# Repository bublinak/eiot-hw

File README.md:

# eiot-hw
Schemes, drawings &amp; other documentation

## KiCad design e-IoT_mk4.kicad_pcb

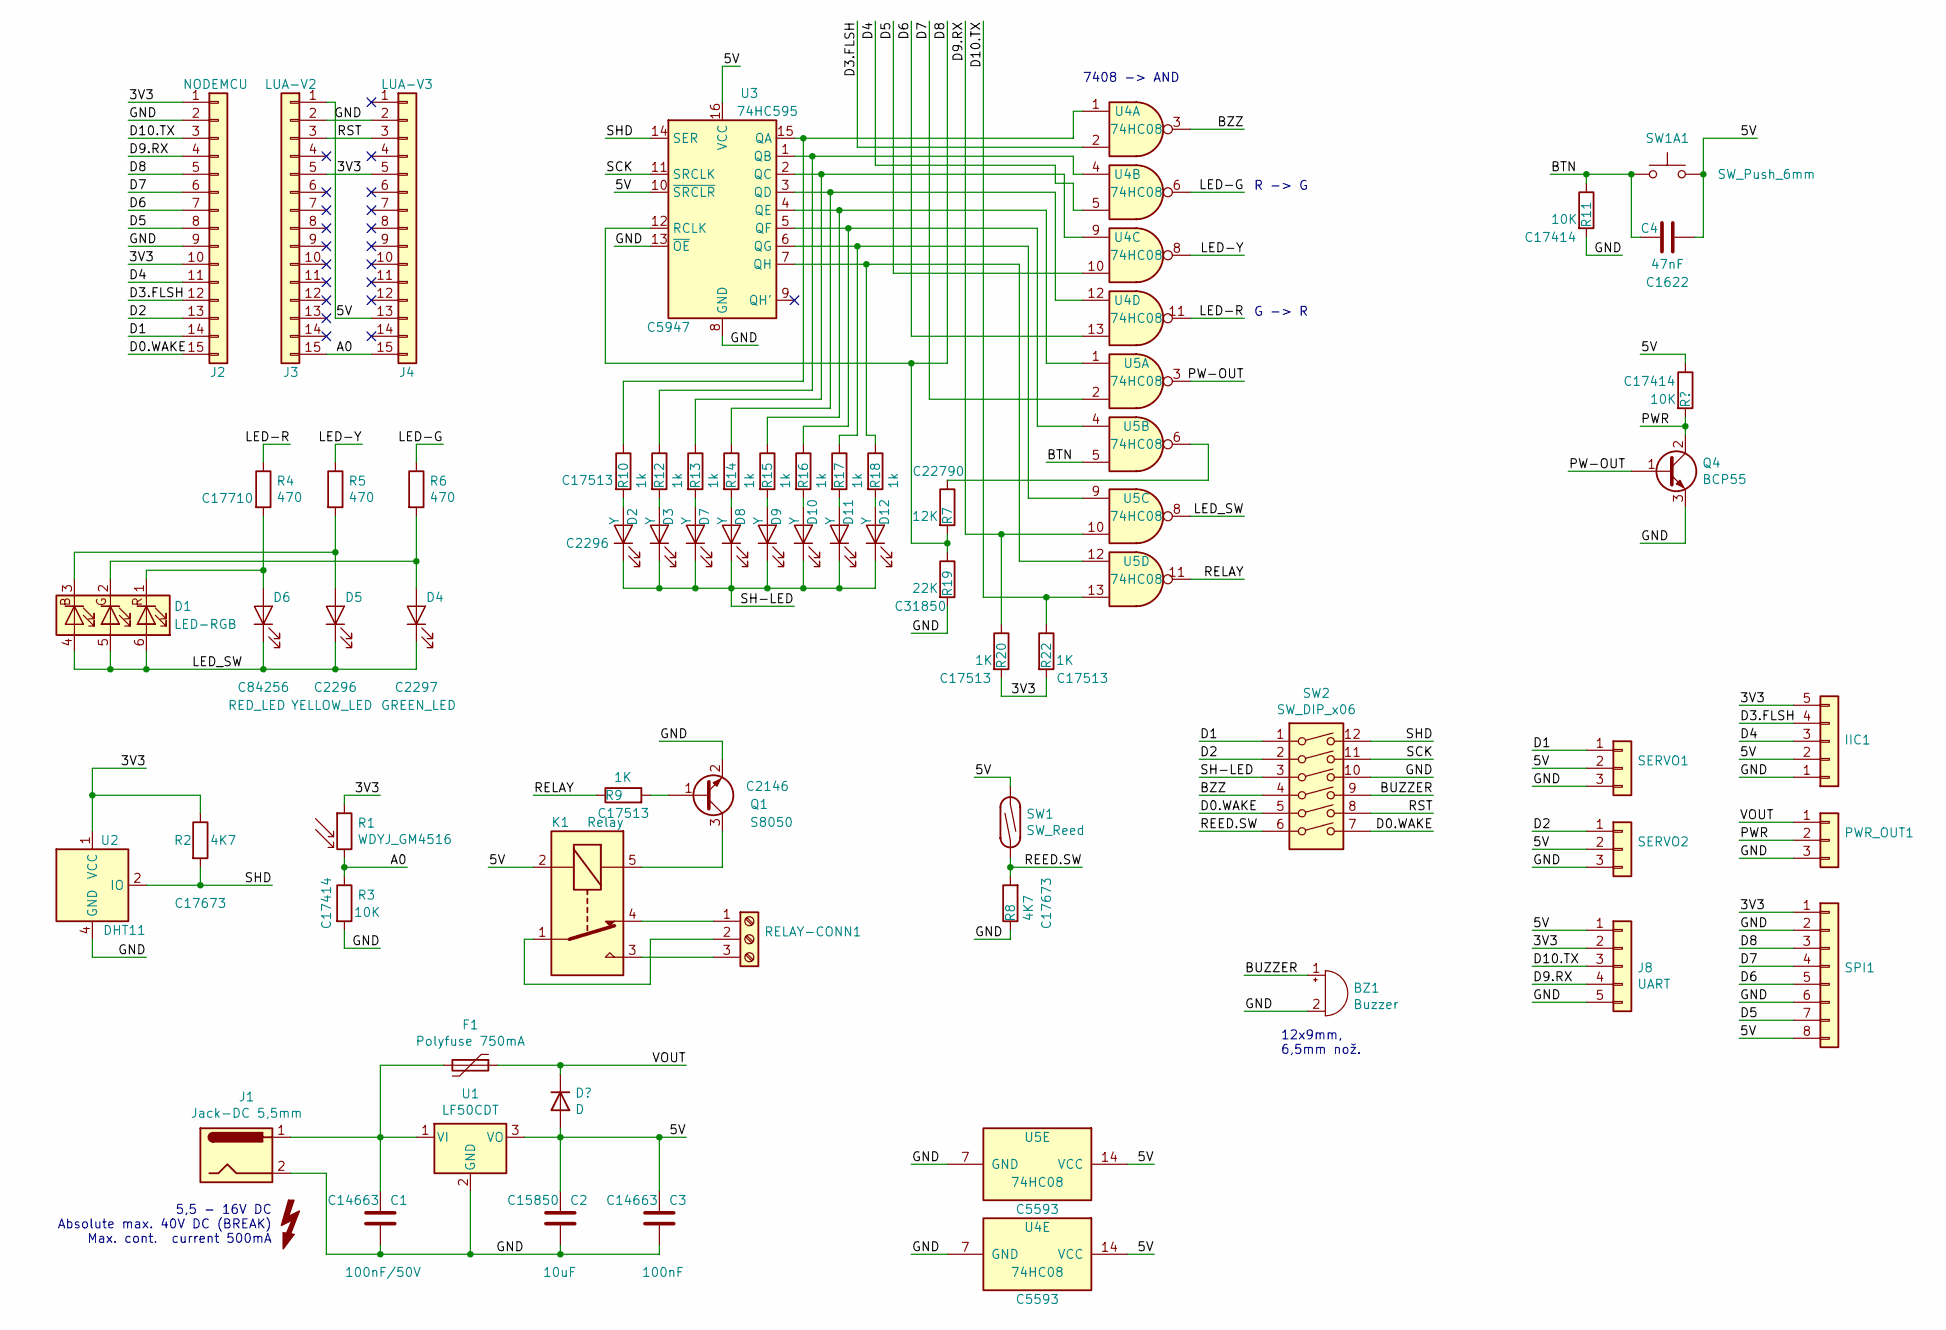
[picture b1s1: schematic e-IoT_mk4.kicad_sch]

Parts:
BZ1: Buzzer; MagneticBuzzer_ProSignal_ABT-410-RC
C1: 100nF/50V; C_0603_1608Metric; LCSC C14663
C2: 10uF; C_0805_2012Metric_Pad1.15x1.40mm_HandSolder; LCSC C15850
C3: 100nF; C_0603_1608Metric_Pad1.05x0.95mm_HandSolder; LCSC C14663
C4: 47nF; C_0603_1608Metric_Pad1.05x0.95mm_HandSolder; LCSC C1622
D1: LED-RGB; LED_RGB_5050-6
D2, D3, D7, D8, D9, D10, D11, D12: Y; LED_0805_2012Metric_Castellated; LCSC C2296
D4: GREEN_LED; LED_0805_2012Metric_Castellated; LCSC C2297
D5: YELLOW_LED; LED_0805_2012Metric_Castellated; LCSC C2296
D6: RED_LED; LED_0805_2012Metric_Castellated; LCSC C84256
F1: Polyfuse 750mA; Fuse_1812_4532Metric_Pad1.30x3.40mm_HandSolder
IIC1: PinSocket_1x05_P2.54mm_Horizontal
J1: Jack-DC 5,5mm; BarrelJack_Horizontal
J2: NODEMCU; PinSocket_1x15_P2.54mm_Vertical
J3: LUA-V2; PinSocket_1x15_P2.54mm_Vertical
J4: LUA-V3; PinSocket_1x15_P2.54mm_Vertical
J8: UART; PinHeader_1x05_P2.54mm_Vertical
K1: Relay; Relay_SPDT_SANYOU_SRD_Series_Form_C
PWR_OUT1: JST_XH_S3B-XH-A-1_1x03_P2.50mm_Horizontal
Q1: S8050; SOT-23; LCSC C2146
Q4: BCP55; SOT-223
R1: WDYJ_GM4516; R_LDR_4.9x4.2mm_P2.54mm_Vertical
R2, R8: 4K7; R_0805_2012Metric_Pad1.15x1.40mm_HandSolder; LCSC C17673
R3, R11: 10K; R_0805_2012Metric_Pad1.15x1.40mm_HandSolder; LCSC C17414
R4, R5, R6: 470; R_0805_2012Metric_Pad1.15x1.40mm_HandSolder; LCSC C17710
R7: 12K; R_0603_1608Metric; LCSC C22790
R9, R20, R22: 1K; R_0805_2012Metric_Pad1.15x1.40mm_HandSolder; LCSC C17513
R10, R12, R13, R14, R15, R16, R17, R18: 1k; R_0805_2012Metric_Pad1.15x1.40mm_HandSolder; LCSC C17513
R19: 22K; R_0603_1608Metric; LCSC C31850
RELAY-CONN1: Screw_Terminal_01x03; TerminalBlock_bornier-3_P5.08mm
SERVO1, SERVO2: PinHeader_1x03_P2.54mm_Vertical
SPI1: PinSocket_1x08_P2.54mm_Horizontal
SW1: SW_Reed; Crystal_AT310_D3.0mm_L10.0mm_Horizontal
SW1A1: SW_Push_6mm; SW_PUSH_6mm_H5mm
SW2: SW_DIP_x06; DIP-12_W7.62mm_Socket_LongPads
U1: LF50CDT; TO-252-2
U2: DHT11; Aosong_DHT11_5.5x12.0_P2.54mm
U3: 74HC595; SOIC-16_3.9x9.9mm_P1.27mm; LCSC C5947
U4: 74HC08; SOIC-14_3.9x8.7mm_P1.27mm
U5: 74HC08

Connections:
/3V3: IIC1.5, J2.1, J2.10, J3.5, J4.5, J8.2, R1.1, R2.1, R20.2, R22.2, SPI1.1, U2.1 (VCC)
/5V: C2.1, C3.1, C4.1, IIC1.2, J3.1, J4.13, J8.1, K1.2, SERVO1.2, SERVO2.2, SPI1.8, SW1.1, SW1A1.2, U1.3 (VO), U3.10 (~SRCLR), U3.16 (VCC), U4.14 (VCC), U5.14 (VCC)
/A0: J3.15, J4.15, R1.2, R3.1
/BTN: C4.2, R11.1, SW1A1.1, U5.5
/BUZZER: BZ1.1 (-), SW2.9
/BZZ: SW2.4, U4.3
/D0.WAKE: J2.15, SW2.5, SW2.7
/D1: J2.14, SERVO1.1, SW2.1
/D2: J2.13, SERVO2.1, SW2.2
/D3.FLSH: IIC1.4, J2.12, U4.2
/D4: IIC1.3, J2.11, U4.5
/D5: J2.8, SPI1.7, U4.10
/D6: J2.7, SPI1.5, U4.13
/D7: J2.6, SPI1.4, U5.2
/D8: J2.5, R7.2, R19.1, SPI1.3, U3.12 (RCLK)
/D9.RX: J2.4, J8.4, R20.1, U5.10
/D10.TX: J2.3, J8.3, R22.1, U5.13
/GND: BZ1.2 (+), C1.2, C2.2, C3.2, IIC1.1, J1.2, J2.2, J2.9, J3.2, J4.2, J8.5, PWR_OUT1.3, Q1.2 (E), Q4.3 (E), R3.2, R8.1, R11.2, R19.2, SERVO1.3, SERVO2.3, SPI1.2, SPI1.6, SW2.10, U1.2 (GND), U2.4 (GND), U3.8 (GND), U3.13 (~OE), U4.7 (GND), U5.7 (GND)
/LED-G: R6.1, U4.6
/LED-R: R4.1, U4.11
/LED-Y: R5.1, U4.8
/LED_SW: D1.4 (BA), D1.5 (GA), D1.6 (RA), D4.1 (K), D5.1 (K), D6.1 (K), U5.8
/PW-OUT: Q4.1 (B), U5.3
/PWR: PWR_OUT1.2, Q4.2 (C), Q4.4 (C)
/REED.SW: R8.2, SW1.2, SW2.6
/RELAY: R9.1, U5.11
/RST: J3.3, J4.3, SW2.8
/SCK: SW2.11, U3.11 (SRCLK)
/SH-LED: D2.1 (K), D3.1 (K), D7.1 (K), D8.1 (K), D9.1 (K), D10.1 (K), D11.1 (K), D12.1 (K), SW2.3
/SHD: R2.2, SW2.12, U2.2 (IO), U3.14 (SER)
/VI: F1.1, PWR_OUT1.1
unnamed: C1.1, F1.2, J1.1, U1.1 (VI)
unnamed: D1.1 (RK), D6.2 (A), R4.2
unnamed: D1.2 (GK), D4.2 (A), R6.2
unnamed: D1.3 (BK), D5.2 (A), R5.2
unnamed: D2.2 (A), R10.2
unnamed: D3.2 (A), R12.2
unnamed: D7.2 (A), R13.2
unnamed: D8.2 (A), R14.2
unnamed: D9.2 (A), R15.2
unnamed: D10.2 (A), R16.2
unnamed: D11.2 (A), R17.2
unnamed: D12.2 (A), R18.2
unnamed: K1.1, RELAY-CONN1.2
unnamed: K1.3, RELAY-CONN1.3
unnamed: K1.4, RELAY-CONN1.1
unnamed: K1.5, Q1.3 (C)
unnamed: Q1.1 (B), R9.2
unnamed: R7.1, U5.6
unnamed: R10.1, U3.15 (QA), U4.1
unnamed: R12.1, U3.1 (QB), U4.4
unnamed: R13.1, U3.2 (QC), U4.9
unnamed: R14.1, U3.3 (QD), U4.12
unnamed: R15.1, U3.4 (QE), U5.1
unnamed: R16.1, U3.5 (QF), U5.4
unnamed: R17.1, U3.6 (QG), U5.9
unnamed: R18.1, U3.7 (QH), U5.12

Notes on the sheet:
5,5 - 16V DC Absolute max. 40V DC (BREAK) Max. cont. current 500mA
R -> G
12x9mm, 6,5mm nož.
7408 -> AND
G -> R

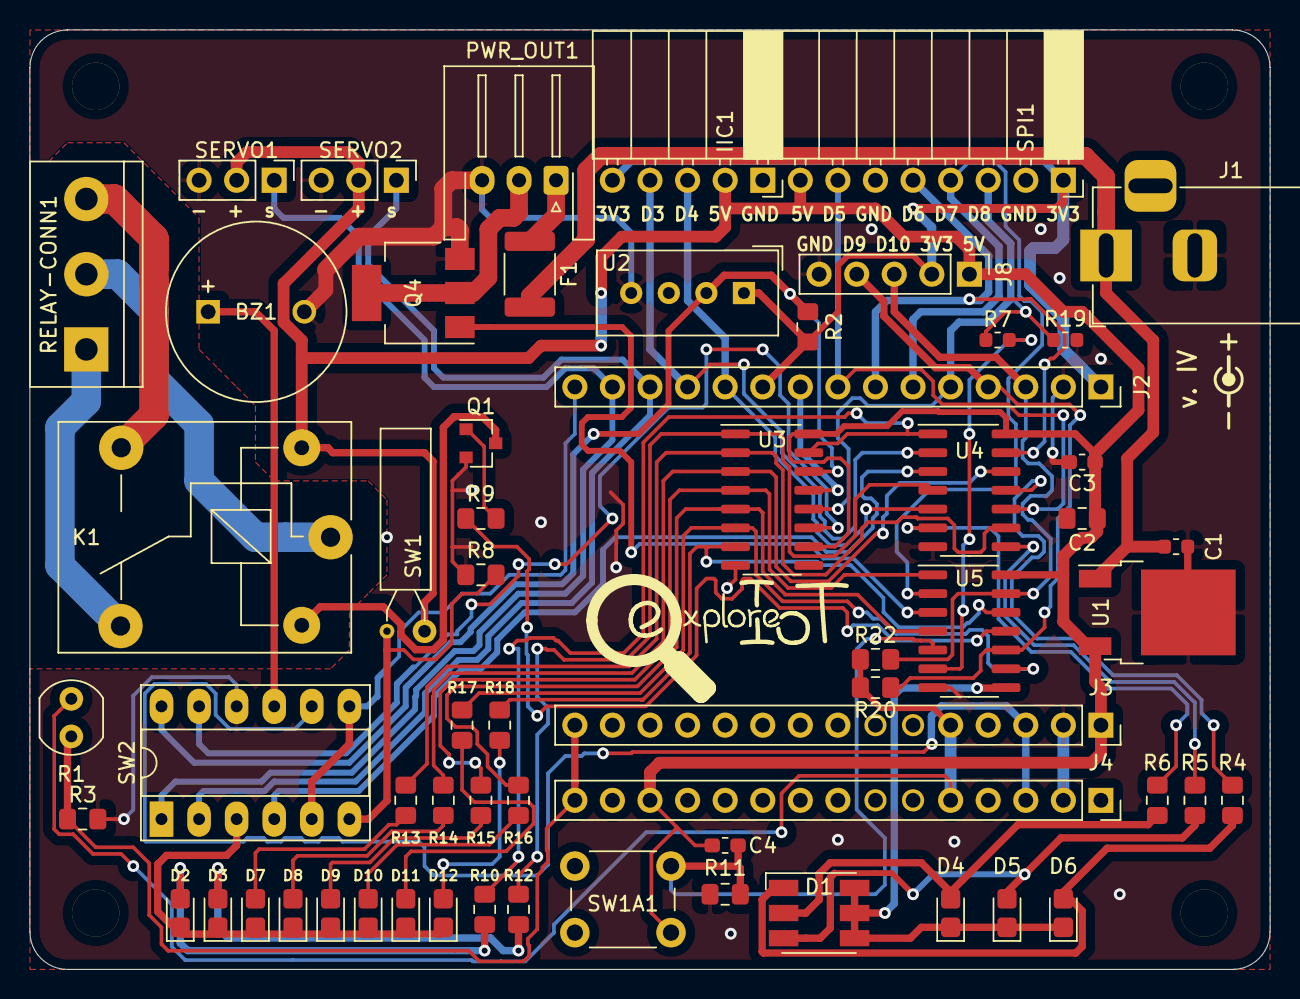
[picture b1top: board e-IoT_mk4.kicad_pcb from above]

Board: 2 copper layers, 83.8 x 63.5 mm, 61 parts (0 on the bottom side), 57 nets.

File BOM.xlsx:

Comment | Designator | Footprint | LCSC
10K | R3 | Resistor_SMD:R_0805_2012Metric_Pad1.15x1.40mm_HandSolder | C17414
RED_LED | D6 | LED_SMD:LED_0805_2012Metric_Castellated | C84256
YELLOW_LED | D5 | LED_SMD:LED_0805_2012Metric_Castellated | C2296
GREEN_LED | D4 | LED_SMD:LED_0805_2012Metric_Castellated | C2297
470 | R4 | Resistor_SMD:R_0805_2012Metric_Pad1.15x1.40mm_HandSolder | C17710
4K7 | R2 | Resistor_SMD:R_0805_2012Metric_Pad1.15x1.40mm_HandSolder | C17673
74HC595 | U3 | Package_SO:SOIC-16_3.9x9.9mm_P1.27mm | C5947
1K | R9 | Resistor_SMD:R_0805_2012Metric_Pad1.15x1.40mm_HandSolder | C17513
S8050 | Q1 | Package_TO_SOT_SMD:SOT-23 | C2146
470 | R5 | Resistor_SMD:R_0805_2012Metric_Pad1.15x1.40mm_HandSolder | C17710
470 | R6 | Resistor_SMD:R_0805_2012Metric_Pad1.15x1.40mm_HandSolder | C17710
1k | R10 | Resistor_SMD:R_0805_2012Metric_Pad1.15x1.40mm_HandSolder | C17513
Y | D2 | LED_SMD:LED_0805_2012Metric_Castellated | C2296
1k | R12 | Resistor_SMD:R_0805_2012Metric_Pad1.15x1.40mm_HandSolder | C17513
1k | R13 | Resistor_SMD:R_0805_2012Metric_Pad1.15x1.40mm_HandSolder | C17513
1k | R14 | Resistor_SMD:R_0805_2012Metric_Pad1.15x1.40mm_HandSolder | C17513
1k | R15 | Resistor_SMD:R_0805_2012Metric_Pad1.15x1.40mm_HandSolder | C17513
1k | R16 | Resistor_SMD:R_0805_2012Metric_Pad1.15x1.40mm_HandSolder | C17513
1k | R17 | Resistor_SMD:R_0805_2012Metric_Pad1.15x1.40mm_HandSolder | C17513
1k | R18 | Resistor_SMD:R_0805_2012Metric_Pad1.15x1.40mm_HandSolder | C17513
Y | D3 | LED_SMD:LED_0805_2012Metric_Castellated | C2296
Y | D7 | LED_SMD:LED_0805_2012Metric_Castellated | C2296
Y | D8 | LED_SMD:LED_0805_2012Metric_Castellated | C2296
Y | D9 | LED_SMD:LED_0805_2012Metric_Castellated | C2296
Y | D10 | LED_SMD:LED_0805_2012Metric_Castellated | C2296
Y | D11 | LED_SMD:LED_0805_2012Metric_Castellated | C2296
Y | D12 | LED_SMD:LED_0805_2012Metric_Castellated | C2296
74HC08 | U5 | Package_SO:SOIC-14_3.9x8.7mm_P1.27mm | C5593
47nF | C4 | Capacitor_SMD:C_0603_1608Metric_Pad1.05x0.95mm_HandSolder | C1622
10K | R11 | Resistor_SMD:R_0805_2012Metric_Pad1.15x1.40mm_HandSolder | C17414
4K7 | R8 | Resistor_SMD:R_0805_2012Metric_Pad1.15x1.40mm_HandSolder | C17673
10uF | C2 | Capacitor_SMD:C_0805_2012Metric_Pad1.15x1.40mm_HandSolder | C15850
100nF/50V | C1 | Capacitor_SMD:C_0603_1608Metric | C14663
100nF | C3 | Capacitor_SMD:C_0603_1608Metric_Pad1.05x0.95mm_HandSolder | C14663
74HC08 | U4 | Package_SO:SOIC-14_3.9x8.7mm_P1.27mm | C5593
22K | R19 | Resistor_SMD:R_0603_1608Metric | C31850
12K | R7 | Resistor_SMD:R_0603_1608Metric | C22790
1K | R20 | Resistor_SMD:R_0805_2012Metric_Pad1.15x1.40mm_HandSolder | C17513
1K | R22 | Resistor_SMD:R_0805_2012Metric_Pad1.15x1.40mm_HandSolder | C17513

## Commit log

2023-11-27 data upload

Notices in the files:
e-IoT_mk4.kicad_pcb:
CC BY-NC-SA 4.0
